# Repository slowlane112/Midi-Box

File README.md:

# MIDI Box

The MIDI Box is a stand-alone music box built around an ESP32-S3 and a SAM2695 General MIDI synth.
It plays MIDI files from an SD card, lets you record and edit your own songs, teaches you to play
the piano, and shows the music on a second screen with 14 visualisers. Plug in a MIDI keyboard
(two DIN inputs or Bluetooth) and play it through the box's own sound.

- **Player**: plays .mid files with tempo, transpose, play modes, mute and solo.
- **Studio**: records, edits and exports your own songs, with or without a keyboard.
- **Learn**: Play Along, scales and chords, Note Reading and Ear Training, with scores and stars.
- **Live In**: play your keyboard through the synth.
- **Visualisers**: 14 ways to watch the music on the bar screen.
- **Transfer**: send songs from your PC to the box.

*The back, left to right: USB-C (power and computer), audio out (red = right, white = left), the
micro SD card slot, then MIDI Thru, MIDI Out and MIDI In 1. MIDI In 2 is on the front.*

The home screen lists everything on screen 1. Screen 2 shows the firmware version, the song you can
resume, and the box's status: free space on the SD card, sound bank, keyboard sound, which DIN input
is in use and the display colour.

---

## The buttons

The buttons do the same thing on every screen.

| Button | Where it is | What it does |
|---|---|---|
| 1 | left of screen 1, the single button at the top | **Shift**: hold it and the bottom row of screen 1 shows the Shift functions |
| 2 / 3 | left of screen 1, the pair below it | Up / down (previous / next) |
| 4 – 8 | the row of five under screen 1, left to right | Soft keys, labelled along the bottom of screen 1. 4 is always **Back**, 8 the main action |
| 9 | under screen 2, left | Next visualiser on screen 2 (Shift + 9: previous) |
| 10 | under screen 2, middle | Next visualiser option: shape, speed, trails… (Shift + 10: previous) |
| 11 | under screen 2, right | Next visualiser colour (Shift + 11: previous) |
| 12 / 13 | right of the MIDI socket, top and bottom | Volume up / down, from any screen |

Holding **button 1** while switching on puts the ESP32-S3 into programming mode (see
*Installing the firmware*).

---

## Player

Pick **Player** on the home screen to browse the SD card. The browser shows folders and MIDI files
and opens in the folder you last played from. From it you can play, copy, move, rename and delete
files, and make new folders.

While a song plays, screen 1 shows the title, its place in the folder, the time, the tempo,
transpose and sound bank, and a level meter for each of the 16 channels.

- **Play modes** (Shift + 4): **Once**, **Repeat**, **Folder** (play the whole folder) and
  **Shuffle** (the folder in a random order).
- **Tempo** 25 – 200 %, **Transpose** ±12 semitones (drums stay as they are).
- **Sound bank**: General MIDI or Roland MT-32.
- **Tracks** (Shift + 8): turn any part off with **Sound**, hear one part on its own with **Solo**,
  or hide a part from the visualisers.
- **Resume** on the home screen carries on where you left off.
- **Auto play** (in Settings) decides whether a song starts as soon as you open it or waits for Play.
- Files that can't be played say why: *This is not a MIDI file we can play*, *Incomplete file*,
  *Could not read the file* or *Not enough memory for this file*. In Folder and Shuffle the box
  moves on to the next song after 3 seconds.

---

## Studio

Make your own songs in **projects** of up to 16 tracks.

- Choose a track and play your DIN or Bluetooth keyboard: you hear that track's instrument.
- **Record** with a count-in, metronome and optional loop for building up a part in layers. Keep or
  discard each take, and undo the last pass.
- **Edit** on a piano roll: copy, cut, paste, delete, duplicate, transpose, change velocity, and
  **quantise** (1/4 to 1/32 and triplets, with strength and swing).
- **Notes**: change single notes, or type a whole tune in with the buttons, no keyboard needed.
  Screen 2 shows the track as notation with note names.
- **Song settings**: tempo, beats per bar, length, GM or MT-32. **Track settings**: instrument (with
  a preview as you scroll), name, channel, volume, mute and solo.
- **Export .mid** (Shift + 5) saves a standard MIDI file you can play in the Player or on a PC.

---

## Learn

Learn to play with your MIDI keyboard connected. The first time, press the lowest and highest key of
your keyboard so the box knows its range.

- **Play Along**: 15 built-in pieces, from *Twinkle Twinkle* and *Ode to Joy* to *Für Elise*,
  *Clair de Lune* and the *Moonlight Sonata* (several in full and easy versions), or any MIDI file
  from the SD card. Play the right hand, left hand or both while the box plays the rest.
  - **Wait mode** waits for you to play each note. **Play mode** keeps going and grades every note
    *Perfect*, *Good*, *Miss* or *Wrong*, with a combo score.
  - Choose the speed, starting bar and count-in, loop four bars, or show note names.
  - Screen 2 is the game: notes fall onto a keyboard the size of yours.
  - Results give 1 – 3 stars, your score, best combo and whether you tend to play early or late.
- **Exercises**: major and minor scales, chords and arpeggios in every key, with the right fingering
  on a grand staff, played along to a metronome. A steadiness meter shows if you rush or drag.
- **Note Reading**: a note appears on the staff; play it before time runs out. Ledger lines, and
  later sharps and flats, come in as you get better.
- **Ear Training**: the box plays, you answer: same or different, up or down, intervals, major or
  minor chords. New levels unlock as you go.
- **Practice stats** on the home screen: your last sessions, total time, stars and songs learnt.

---

## Live In

Play a keyboard through the box's synth. Choose the input (back or front DIN socket, or Bluetooth),
the sound bank and the instrument, which you hear as you scroll through them. The screen shows
activity on each channel and the last message received.

- **Keyboard sound** (Shift + 8, or in Settings) turns the synth on or off for your keyboard. With
  it off the visualisers still follow what you play.
- **Panic** stops every sounding note.
- **Bluetooth MIDI**: 5 reconnects the last device, Shift + 5 searches for a new one.

The **MIDI Thru** socket passes everything from MIDI In 1 (the back socket) straight on to other
gear.

---

## Visualisers

Screen 2 shows the music while you play or listen. Button 9 steps through them, button 10 changes
the option and button 11 the colour. Hold Shift (button 1) with any of the three to go back one.
Each one remembers its own settings.

| Visualiser | Button 10 | Button 11 |
|---|---|---|
| **Piano**: keys light up, with note names and how hard each was played | note names on / off | key colour |
| **Spectrum Analyser**: 16 bars from 31 Hz to 16 kHz, the way a real analyser would show the sound | peak line on / off | bar colour |
| **Staff**: the music scrolling on a grand staff | all channels or one | by channel or one colour |
| **Chords**: the chord name, its notes and the progression | all channels or one | colour |
| **Piano Roll**: notes scrolling past | speed | background |
| **Constellation**: a glowing orb for every note in a starry sky | blobs on / off | background |
| **Embers**: sparks drift off every note, with turning rings behind | rings on / off | background |
| **Warp**: a twisting tunnel, with shapes that change on the drums | shape | background |
| **Psychedelic**: a swirling pattern with waves on the drums | shape | its own colours |
| **Pulse**: flowing plasma with rings for each note | ring shape | colour or Rainbow |
| **Fireworks**: a burst for every note under a starry sky | trails on / off | by channel or one colour |
| **Kaleidoscope**: mirrored shards for every note, rings for the drums | 6 / 8 / 12 slices | background |
| **Synthwave**: a retro sunset with mountains that move with the music | grid speed | theme: Classic, Outrun, Ice, Toxic |
| **Spirograph**: glowing curves shaped by the chords you play | trails on / off | colour or Rainbow |

The colours are Green, Blue, Amber, Purple, Pink, Cyan, Red and White. The last choice on button 11
is **Cycle**, which slowly fades from one colour to the next every 8 seconds.

---

## Getting songs onto the box

Copy .mid files onto the SD card with a card reader, in any folders you like, or send them from a
PC over Bluetooth:

- `extra/midi_box_transfer.py` sends one or more files from Linux or Windows.
  `--install` adds it to the right-click menu (Nemo on Linux, *Send to* on Windows).
  See `extra/midi_box_transfer.txt`.
- The box asks you to accept or decline, then saves the files in `/downloads`.

On the SD card:

| Folder | What's in it |
|---|---|
| any folder you like | your MIDI files (.mid) |
| `/downloads` | files sent from a PC |
| `/projects` | Studio projects (.mbp) and the .mid files you export |
| `/learn` | your keyboard range, best scores, stars and practice time |

---

## Settings

- **Display brightness** and **Display colour** (the highlight colour of the menus).
- **Sound bank**: General MIDI or Roland MT-32.
- **Keyboard sound**: play the MIDI inputs through the synth.
- **Auto play**: start a song as soon as it is opened, or wait for Play.
- **Visualiser**: which one is on screen 2.
- **About**: the firmware version.

---

## Building a MIDI Box

Everything plugs into one main board: the ESP32-S3 board sits on it, and every other part connects
to it with a 2-pin to 8-pin lead. You need to be comfortable soldering through-hole parts (and one
small surface-mount transistor).

### What you need

**Modules and panel parts**

| | Qty | Part | Used for |
|---|---|---|---|
|  | 1 | ESP32-S3 Development Board N16R8, 44 pin (DevKitC-1) | the brain |
|  | 1 | 2.4" 240 × 320 TFT LCD module (ST7789V, SPI, 8 pins) | screen 1 |
|  | 1 | 2.79" 142 × 428 bar-type IPS TFT LCD module (NV3007, SPI, 8 pins) | screen 2 |
|  | 1 | MIDI Digital Music Module SAM2695 | the synth |
|  | 1 | Micro SD card module (Open-Smart "TF Card Breakout") | songs and settings |
|  | 1 | USB Type-C female to DIP breakout board (HW-189) | power and USB |
|  | 4 | DIN 5-pin female round vertical socket | MIDI In 1, In 2, Out, Thru |
|  | 2 | Female RCA panel-mount socket (red and white) | audio out |
|  | 1 | 3.5 mm stereo audio plug | from the synth to the RCA sockets |
|  | 1 | 10 × 21 mm rocker switch KCD1 | power |
|  | 13 | Mini push button, 4.5 × 4.5 × 3.8 mm | the 13 buttons |

**Main board parts** (resistors ¼ W)

| Qty | Part | Where |
|---|---|---|
| 2 | 6N137 optocoupler (DIP-8) and a DIP-8 socket for each | IC1 MIDI In 2, IC2 MIDI In 1 |
| 1 | SN74HCT14N hex Schmitt trigger (DIP-14) and a DIP-14 socket | IC3 MIDI Out and Thru |
| 1 | AO3401A P-channel MOSFET (SOT-23, surface mount) | Q1 screen backlight |
| 4 | 10 kΩ resistor | R1, R2, R4, R6 |
| 6 | 220 Ω resistor | R3, R5, R7, R8, R9, R10 |
| 2 | 1N4148 diode | D1, D2 |
| 3 | 100 nF ceramic capacitor | C1, C2, C3 (one beside each chip) |
| 2 | 5.1 kΩ resistor | on the USB-C breakout (see below) |
| 2 | 1 × 22 female header, 2.54 mm | for the ESP32-S3 board |
| 2 | 1 × 8 female header | J7, J8 screens |
| 2 | 1 × 6 female header | J2 buttons 4–8, J9 SD card |
| 3 | 1 × 4 female header | J1 buttons 1–3, J3 buttons 9–11, J10 USB-C |
| 2 | 1 × 3 female header | J4 buttons 12–13, J6 synth |
| 5 | 1 × 2 female header | J5 power switch, J11 – J14 MIDI sockets |
| 1 | 90 × 70 mm prototype board, 2.54 mm pitch | the main board |
| – | small pieces of prototype board | four strips for the buttons, and one to mount the USB-C breakout |

**Screws**

| Qty | Screw | Used for |
|---|---|---|
| 25 | M2 × 6 mm | all the parts inside: screens, button strips, main board, USB-C board, SAM2695, SD module |
| 8 | M3 × 8 mm button head | front panel to the case |
| 6 | M3 × 25 mm socket cap head | case top to case bottom |

You also need the 3D-printed case and parts (see [The case](#the-case)), leads with 2.54 mm pins or
housings to join each part to its header (Dupont leads, crimped housings or wire soldered to header
pins all work), a micro SD card, and a USB-C power supply or cable.

### The main board

Build the board on a standard **90 × 70 mm prototype board**: the case's screw holes are made to
fit it (four M2 holes, 2 mm in from each corner, 86 × 66 mm apart). A PCB design of the same board
is included too, but it has not been made or tested yet: see
[*The PCB (work in progress)*](#the-pcb-work-in-progress) below.

**Circuit**

*MIDI In 1 and 2, MIDI Out and MIDI Thru:*

*The ESP32-S3 board, the GPIO0 pull-up and the screen backlight switch:*

*The connectors, pin 1 at the top of each:*

Labels with the same name are joined: every `GPIO17` is one wire, every `GND` is one wire, and so on.
The ESP32-S3 board supplies the 3.3 V; the 5 V comes from the USB-C socket through the power switch.

**The prototype board build (tested)**

*The ESP32-S3 board runs along the bottom, USB end on the left and its antenna on the right, clear
of everything else. The 74HCT14 (left) and the two 6N137s sit in sockets along the top, each with
its 100 nF capacitor beside it and its resistors and diode next to it. The connector headers are a
long row across the middle and two columns down the right-hand side. The AO3401A is on the
underside, so you can't see it here.*

Keep the area to the right of the ESP32-S3 board's antenna free of wires and copper, so Bluetooth
works well.

**PCB layout** (top view, the square pad is pin 1 of each part). This is how the parts sit on the
PCB design. It is laid out differently from the prototype board above, and you don't have to copy
either one exactly: any layout that makes the connections in the circuit works.

**Soldering order**

1. **Q1** (AO3401A) first, while the board is flat: pin 1 (gate) to R1 and GPIO10, pin 2 (source)
   to 3.3 V, pin 3 (drain) to the BL pin of both screen headers. On a prototype board it can go on
   the **underside**, as in the photo; its three pins still connect the same way.
2. **Resistors** and **diodes**. Each 1N4148 goes across the LED of its 6N137, with the **band
   (cathode) to pin 2** and the other end to pin 3.
3. **IC sockets**, with the notch at pin 1, then the **capacitors**, each from 5 V to GND right next
   to its chip.
4. **Headers**: the two 1 × 22 rows for the ESP32-S3 board (11 holes apart, 27.94 mm), then the
   connector headers.
5. Check every joint, then fit the chips into their sockets, notch to notch.

### The PCB (work in progress)

> ⚠️ **Not tested.** This PCB has not been manufactured or tried in a MIDI Box yet. It is shared so
> you can see where the project is going, check it, or improve it. If you order it, you do so at your
> own risk. The prototype-board build above is the one that is known to work.

The KiCad project is in [`hardware/main_board/`](hardware/main_board/):

| File | What it is |
|---|---|
| `midibox_main.kicad_sch` | the circuit (the same as the pictures above) |
| `midibox_main.kicad_pcb` | the 90 × 70 mm, 2-layer board, routed, with a ground pour on both sides |
| `midibox_main.kicad_pro` | the KiCad project with the track widths and clearances |
| `BOM.csv` | the parts on the board |
| `WIRING.md` | every connection, net by net |
| `midibox_main_gerbers.zip` | the Gerber and drill files, ready to upload to a PCB maker |
| `gerbers/` | the same Gerber and drill files, unzipped |

It uses the same parts, the same connectors and the same pin order as the prototype-board build, so
everything else in this guide applies to it. The four M2 holes are in the same places.

**Where it stands**

- It was drawn and routed in KiCad 10 and passes its design-rule check with these known exceptions:
  - Some resistor, diode and capacitor outlines overlap slightly on paper. The real parts sit about
    1 mm apart.
  - One GND pin of the ESP32-S3 board (the bottom row, at the right-hand end) is not joined to
    the board's ground, because it sits next to the antenna area, which is kept free of copper.
    The ESP32-S3 board joins all its GND pins itself.
  - The pin labels on the silkscreen are a little smaller than some makers like (0.7 mm).
- Nothing on the board has been checked on real hardware: the footprints against your actual
  parts, the ESP32-S3 board's two pin rows (27.94 mm apart), the MOSFET's pinout, or the board
  in the case.

**If you want to try it**

1. Open the project in KiCad and run **Inspect → Design Rules Checker** yourself.
2. Compare each footprint with the parts you have, especially the ESP32-S3 board and Q1 (AO3401A).
3. Upload `midibox_main_gerbers.zip` to a PCB maker: 2 layers, 90 × 70 mm, 1.6 mm thick. (If you
   change the design, make new ones with **File → Fabrication Outputs**.)
4. Please share what you find. Corrections will go into a tested version.

### Connecting the parts

Pin 1 of each header is the square pad in the layout above. All the button and screen headers have
pin 1 (and GND) at the bottom.

**Screens**: both modules have the same 8 pins in the same order, so each plugs in pin for pin.

| Header pin | 1 | 2 | 3 | 4 | 5 | 6 | 7 | 8 |
|---|---|---|---|---|---|---|---|---|
| Screen pin | GND | VCC / VDD | SCL | SDA | RES | DC | CS | BL |
| J7 screen 1 (2.4") | GND | 3.3 V | GPIO15 | GPIO6 | GPIO13 | GPIO21 | GPIO12 | backlight |
| J8 screen 2 (2.79") | GND | 3.3 V | GPIO8 | GPIO7 | GPIO14 | GPIO18 | GND | backlight |

**SD card module (J9)**: 6 of its 9 pins. Leave CDN, DAT1 and DAT2 unconnected.

| J9 pin | 1 | 2 | 3 | 4 | 5 | 6 |
|---|---|---|---|---|---|---|
| Module pin | GND | VCC | DO | DI | SCLK | CS |

**Synth (J6)**: to the SAM2695's 3-pin **MIDI** connector: pin 1 → **G**, pin 2 → **V**,
pin 3 → **S**.

**Audio**: solder a short cable from the 3.5 mm plug to the two RCA sockets and plug it into the
SAM2695's headphone jack:

- **Tip** → left RCA (white)
- **Ring** → right RCA (red)
- **Sleeve** → the ground tag of both RCA sockets

**USB-C (J10)**: the breakout is soldered by its header pins onto a small piece of prototype board,
which is screwed into the case behind the USB-C hole.

The HW-189 has 12 pins in two columns (rows counted from the GND end):

| Row | Inner column (next to the labels) | Outer column |
|---|---|---|
| 1 | GND | GND |
| 2 | SBU1 | **CC2** |
| 3 | DN1 | DP2 |
| 4 | DP1 | DN2 |
| 5 | **CC1** | SBU2 |
| 6 | VCC | VCC |

1. On the mounting board, solder **one 5.1 kΩ resistor from CC1 to GND** and **another from CC2 to
   GND**. Use two separate resistors. Without them a USB-C charger or a C-to-C cable won't switch the
   5 V on.
2. Join the two **GND** pins, and the two **VCC** pins.
3. Link **DN1 to DN2** and **DP1 to DP2** (the short blue and yellow links in the photo) so the plug
   works either way up. Leave SBU1 and SBU2 unconnected.
4. Connect it to J10:

| J10 pin | 1 | 2 | 3 | 4 |
|---|---|---|---|---|
| Breakout | VCC | GND | DP (D+) | DN (D−) |

**Power switch (J5)**: the rocker switch goes between pin 1 (the ESP32-S3 board's 5 V) and pin 2
(5 V from the USB-C socket).

**Back panel**: this is where each socket goes (seen from the back of the box). MIDI In 2 is the
one on the front panel.

**MIDI sockets**: two wires each. Header **pin 1 → DIN pin 4**, **pin 2 → DIN pin 5**. Pin 2 of the
DIN socket is the centre one, with 4 and 5 either side of it; check the numbers on your socket.

| Header | Socket |
|---|---|
| J14 | MIDI In 1 (back) |
| J11 | MIDI In 2 (front) |
| J13 | MIDI Out |
| J12 | MIDI Thru |

**Buttons**: numbered as in the picture under *The buttons*. Each button goes between its pin and
the GND pin of the same header. The 4-pin push
buttons are joined in pairs inside, so use two pins on opposite corners.

| Header | Pin 1 | Pin 2 | Pin 3 | Pin 4 | Pin 5 | Last pin |
|---|---|---|---|---|---|---|
| J1 | button 1 (Shift) | button 2 (up) | button 3 (down) | GND | | |
| J2 | button 4 (Back) | button 5 | button 6 | button 7 | button 8 | GND |
| J3 | button 9 | button 10 | button 11 | GND | | |
| J4 | button 12 | button 13 | GND | | | |

Label each lead as you make it, and keep each connector's leads together in a bundle held with a
couple of small clips. It keeps the inside tidy, and you can follow every lead when checking it.

### The case

The case and its small parts are 3D printed. The print files are in
[`hardware/case/`](hardware/case/); the screws are listed under [What you need](#what-you-need).

| File | Print | What it's for |
|---|---|---|
| `case_bottom.stl` | 1 | bottom half of the case |
| `case_top.stl` | 1 | top half of the case |
| `case_front.stl` | 1 | front panel |
| `button_main.stl` | 13 | button caps (see the note below) |
| `button_small_tolerance.stl` | – | looser button cap, only if needed |
| `button_high_tolerance.stl` | – | loosest button cap, only if needed |
| `midi_module_bottom_mount.stl` | 1 | goes under the SAM2695 module |
| `midi_module_top_washer.stl` | 2 | go on top of the SAM2695 module, under the screw heads |
| `screen_2_clamp.stl` | 1 | holds down the side of screen 2 that has no mounting holes |
| `sd_card_gap_fill.stl` | 1 | glued to the SD card module (see below) |
| `front_label_plate.stl` | 1 | front label |
| `back_label_plate.stl` | 1 | back label |

- **Button caps:** print one `button_main` first and try it. If it doesn't move freely when you
  press it, try `button_small_tolerance`, and if that is still tight, `button_high_tolerance`. Then
  print all 13 in the size that works.
- **SAM2695 module:** its mounting holes are extra large, so a screw head alone won't hold it. Fit
  the printed bottom mount under the module and a top washer over each hole.
- **SD card gap fill:** glue it to the SD card module. It closes the gap between the module and the
  case, so a card can't be pushed into the case instead of into the module's slot.
- **Tip:** for a perfect alignment of the screens in the front panel, you can enlarge the mounting
  holes on the LCD screen boards slightly. This gives each screen a little room to move so you can
  line it up exactly before tightening the screws.

**The front panel**

*Seen from behind, so left and right are swapped. The two screens are screwed to the panel; the
2.79" bar screen has a printed holder over its 8-pin header. The buttons are soldered onto four
small strips of prototype board, each held by two screws, with the buttons pushing through the
panel under the red caps: buttons 1–3 (on the right here), 4–8 (long strip at the bottom), 9–11
(middle strip) and 12–13 (small strip on the left). MIDI In 2 and the power switch are mounted
straight into the panel.*

**Fitting it into the case**

*First, before any wiring: the front panel is fitted, and the main board with the ESP32-S3 sits in
the base. The two posts on the left are for the SAM2695 module. On the back panel, from the left:
USB-C, the SD slot, the RCA sockets, and the three MIDI sockets. The RCA sockets can go either way
up, as long as the plug's tip goes to the white one and its ring to the red one.*

*Then everything wired up. The SD module, RCA sockets and USB-C breakout are fixed along the back
wall, the SAM2695 is screwed down on spacers on the right, and each connector's leads run to the
main board in their own clipped bundle.*

### Installing the firmware

1. Download the `.bin` file from the releases page.
2. Download **esptool** from https://github.com/espressif/esptool/releases.
3. Hold **button 1** while switching the box on to put it into programming mode, then connect the
   box's USB-C socket to your computer.
4. Flash the image:

   **Windows**
   ```
   esptool.exe --chip esp32s3 write_flash 0x0 "Midi_Box_x.x.x.bin"
   ```
   Replace `Midi_Box_x.x.x.bin` with the name of your file.

   **Linux**
   ```
   ./esptool --chip esp32s3 write_flash 0x0 Midi_Box_*.bin
   ```
   If esptool can't find the box, add the `--port` option, for example `--port COM5` on Windows or
   `--port /dev/ttyACM0` on Linux.
5. Switch the box off and on again.

**Building it yourself:** install ESP-IDF 6.0, then run `idf.py set-target esp32s3` and
`idf.py build flash`.

You can also flash the ESP32-S3 board through its own USB-C ports before it goes into the box. In
the finished box those ports aren't used.

### First switch-on

- Both screens light up after a moment: the home menu on screen 1 and the status on screen 2.
- **A screen stays dark or white**: check its 8 wires, the 3.3 V, and the backlight (BL) wire.
- **A button does nothing**: check the GND wire of its header.
- **No sound**: check the synth's G / V / S wiring and the audio cable, and press button 12 to turn
  the volume up.
- **MIDI keyboard not heard**: open **Live In**; if the activity lights don't move, swap the two
  wires of that MIDI socket.
- **SD card: no card** on screen 2: check the 6 SD wires and that the card is FAT32.

**Tip: power it from a USB adapter.** A computer's USB port often can't supply enough current for the
MIDI Box. If it can't, the box will now and then reset itself (a "brownout"). For normal use, run it
from a USB wall adapter. If your computer can't power it reliably, only use the computer while you're
putting the firmware on.

### The SD card

Use a micro SD card formatted as **FAT32**. Copy your MIDI files into any folders you like; the box
makes its own folders (`/downloads`, `/projects`, `/learn`) when it needs them.

---

*Credits: the Moonlight Sonata arrangements in Learn come from the Mutopia Project (CC BY-SA 2.5),
see `tools/learn_midi/CREDITS.txt`.*

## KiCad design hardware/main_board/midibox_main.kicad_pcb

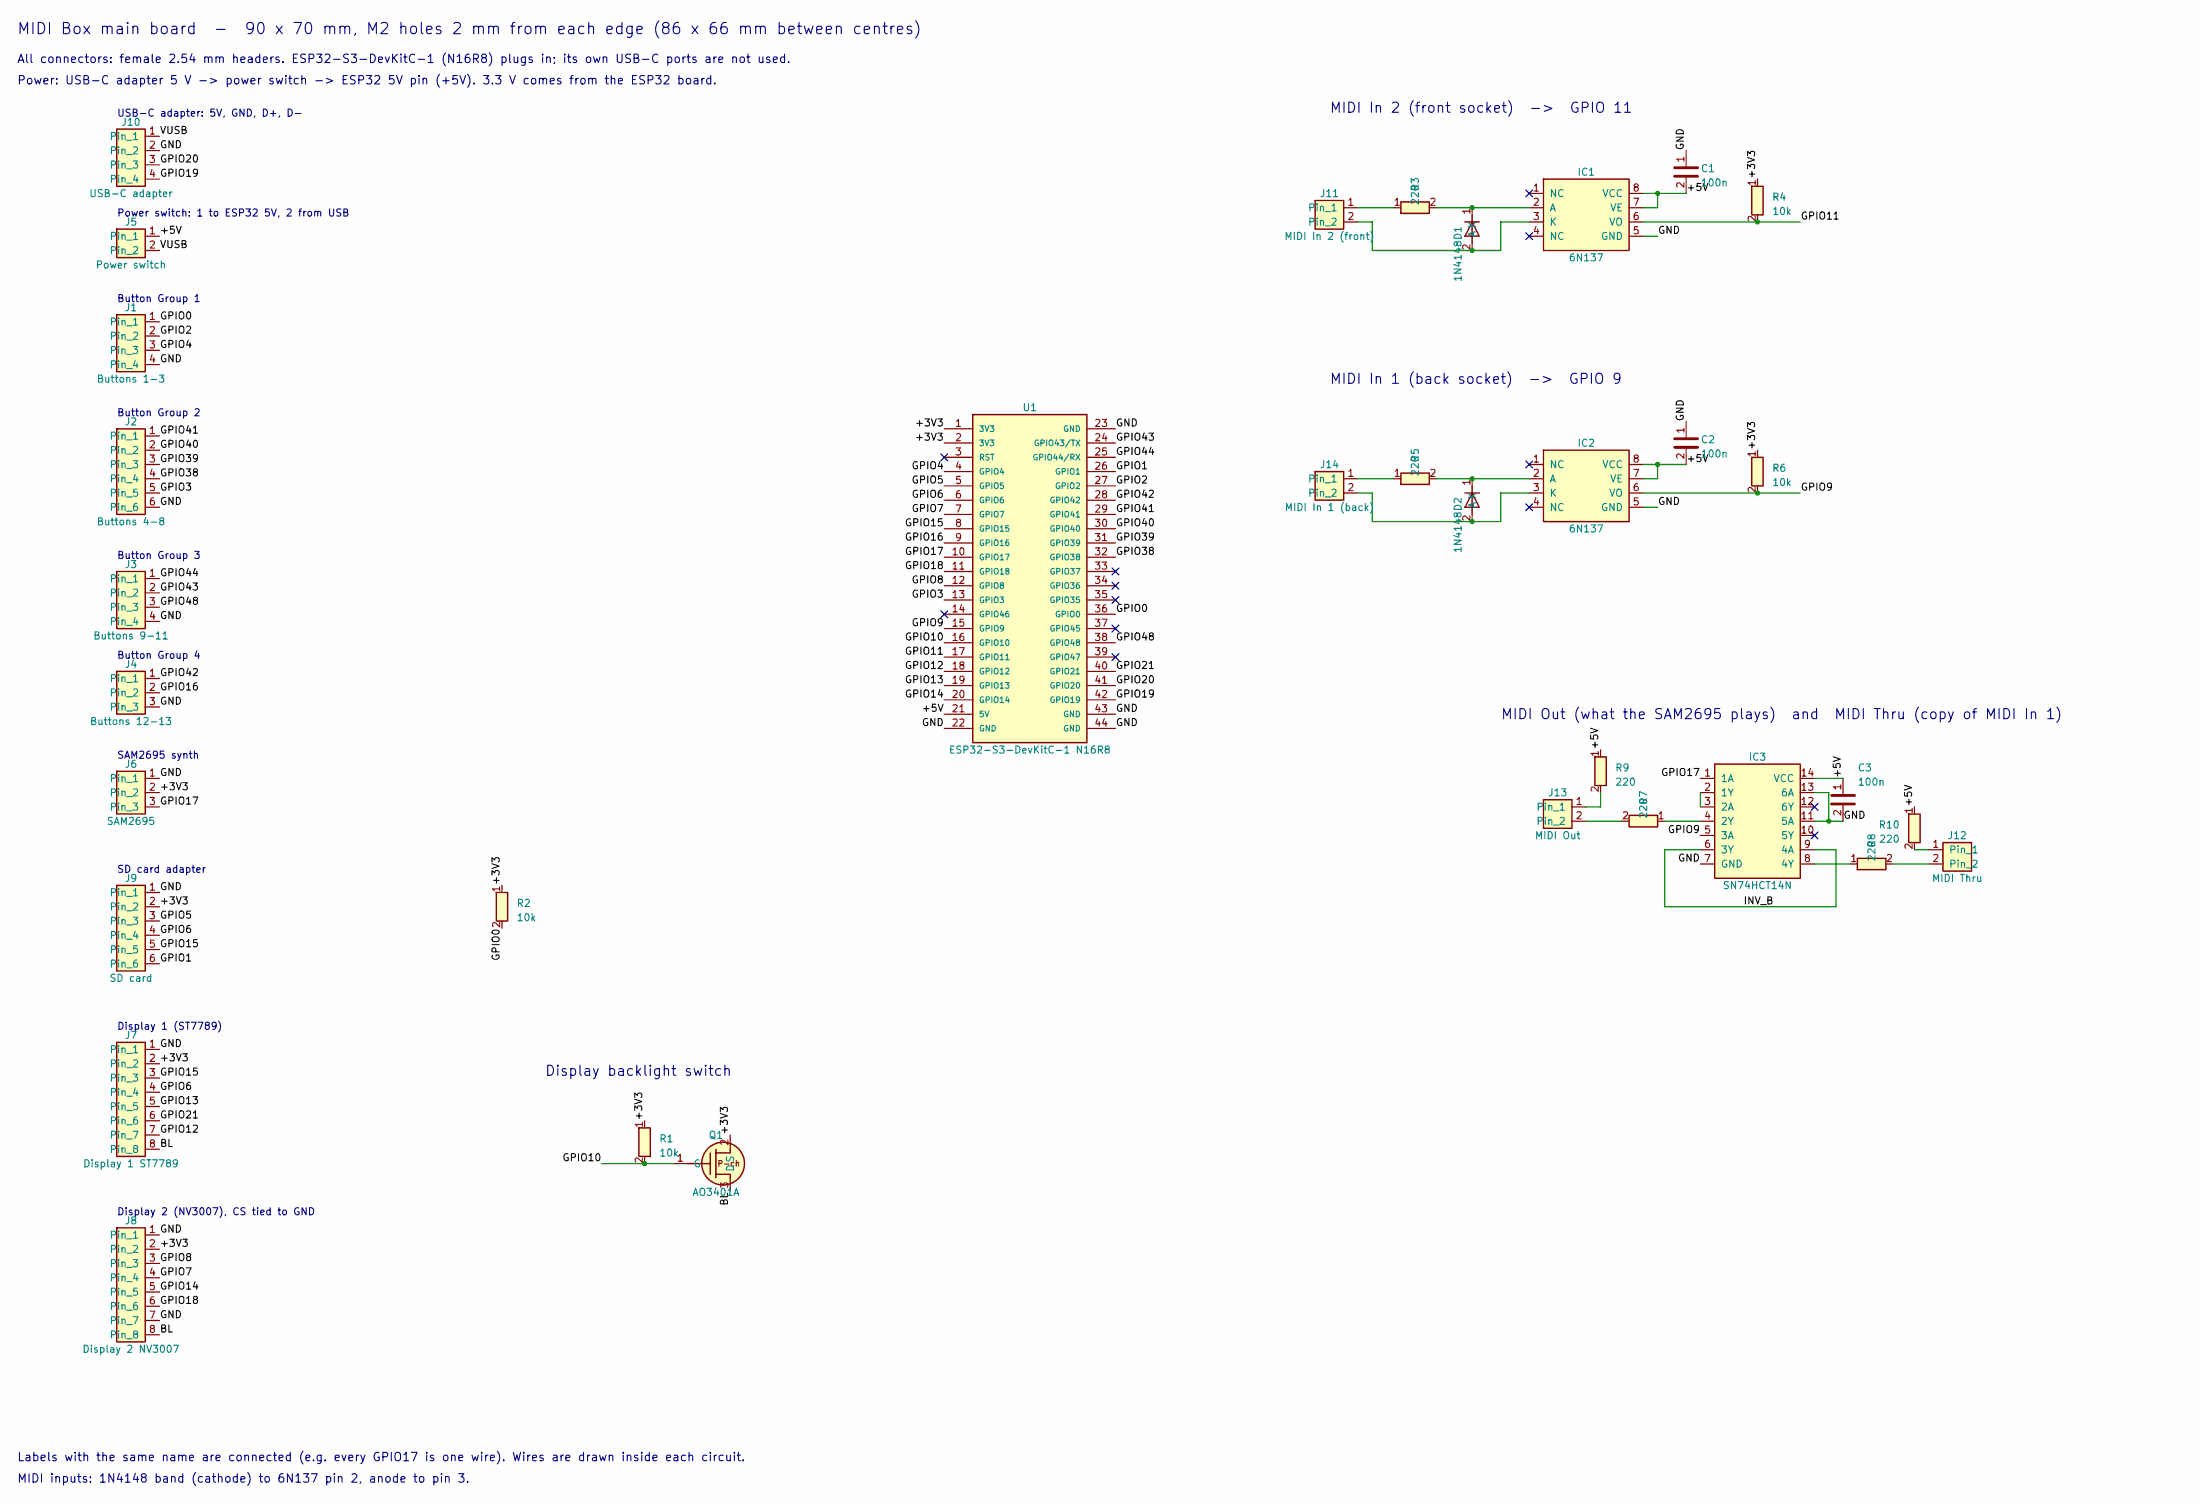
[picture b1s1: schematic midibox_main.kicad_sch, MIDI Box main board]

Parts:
C1, C2, C3: 100n; C_Disc_D3.0mm_W2.0mm_P2.54mm
D1, D2: 1N4148; D_DO-35_SOD27_P7.62mm_Horizontal
IC1, IC2: 6N137; DIP-8_W7.62mm_Socket
IC3: SN74HCT14N; DIP-14_W7.62mm_Socket
J1: Buttons 1-3; PinSocket_1x04_P2.54mm_Vertical
J2: Buttons 4-8; PinSocket_1x06_P2.54mm_Vertical
J3: Buttons 9-11; PinSocket_1x04_P2.54mm_Vertical
J4: Buttons 12-13; PinSocket_1x03_P2.54mm_Vertical
J5: Power switch; PinSocket_1x02_P2.54mm_Vertical
J6: SAM2695; PinSocket_1x03_P2.54mm_Vertical
J7: Display 1 ST7789; PinSocket_1x08_P2.54mm_Vertical
J8: Display 2 NV3007; PinSocket_1x08_P2.54mm_Vertical
J9: SD card; PinSocket_1x06_P2.54mm_Vertical
J10: USB-C adapter; PinSocket_1x04_P2.54mm_Vertical
J11: MIDI In 2 (front); PinSocket_1x02_P2.54mm_Vertical
J12: MIDI Thru; PinSocket_1x02_P2.54mm_Vertical
J13: MIDI Out; PinSocket_1x02_P2.54mm_Vertical
J14: MIDI In 1 (back); PinSocket_1x02_P2.54mm_Vertical
Q1: AO3401A; SOT-23
R1, R2, R4, R6: 10k; R_Axial_DIN0207_L6.3mm_D2.5mm_P10.16mm_Horizontal
R3, R5, R7, R8, R9, R10: 220; R_Axial_DIN0207_L6.3mm_D2.5mm_P10.16mm_Horizontal
U1: ESP32-S3-DevKitC-1 N16R8; ESP32-S3-DevKitC-1_2x22_W27.94mm

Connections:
+3V3: J6.2 (+3V3), J7.2 (+3V3), J8.2 (+3V3), J9.2 (+3V3), Q1.2 (S), R1.1 (+3V3), R2.1 (+3V3), R4.1 (+3V3), R6.1 (+3V3), U1.1 (3V3), U1.2 (3V3)
+5V: C1.2 (+5V), C2.2 (+5V), C3.1 (+5V), IC1.7 (VE), IC1.8 (VCC), IC2.7 (VE), IC2.8 (VCC), IC3.14 (VCC), J5.1 (+5V), R9.1 (+5V), R10.1 (+5V), U1.21 (5V)
BL: J7.8 (BL), J8.8 (BL), Q1.3 (D)
GND: C1.1 (GND), C2.1 (GND), C3.2 (GND), IC1.5 (GND), IC2.5 (GND), IC3.7 (GND), IC3.11 (5A), IC3.13 (6A), J1.4 (GND), J2.6 (GND), J3.4 (GND), J4.3 (GND), J6.1 (GND), J7.1 (GND), J8.1 (GND), J8.7 (GND), J9.1 (GND), J10.2 (GND), U1.22 (GND), U1.23 (GND), U1.43 (GND), U1.44 (GND)
GPIO0: J1.1 (GPIO0), R2.2 (GPIO0), U1.36 (0)
GPIO1: J9.6 (GPIO1), U1.26 (1)
GPIO2: J1.2 (GPIO2), U1.27 (2)
GPIO3: J2.5 (GPIO3), U1.13 (3)
GPIO4: J1.3 (GPIO4), U1.4
GPIO5: J9.3 (GPIO5), U1.5
GPIO6: J7.4 (GPIO6), J9.4 (GPIO6), U1.6
GPIO7: J8.4 (GPIO7), U1.7
GPIO8: J8.3 (GPIO8), U1.12 (8)
GPIO9: IC2.6 (VO), IC3.5 (3A), R6.2 (GPIO9), U1.15 (9)
GPIO10: Q1.1 (G), R1.2 (GPIO10), U1.16 (10)
GPIO11: IC1.6 (VO), R4.2 (GPIO11), U1.17 (11)
GPIO12: J7.7 (GPIO12), U1.18 (12)
GPIO13: J7.5 (GPIO13), U1.19 (13)
GPIO14: J8.5 (GPIO14), U1.20 (14)
GPIO15: J7.3 (GPIO15), J9.5 (GPIO15), U1.8 (15)
GPIO16: J4.2 (GPIO16), U1.9 (16)
GPIO17: IC3.1 (1A), J6.3 (GPIO17), U1.10 (17)
GPIO18: J8.6 (GPIO18), U1.11 (18)
GPIO19: J10.4 (GPIO19), U1.42 (19)
GPIO20: J10.3 (GPIO20), U1.41 (20)
GPIO21: J7.6 (GPIO21), U1.40 (21)
GPIO38: J2.4 (GPIO38), U1.32 (38)
GPIO39: J2.3 (GPIO39), U1.31 (39)
GPIO40: J2.2 (GPIO40), U1.30 (40)
GPIO41: J2.1 (GPIO41), U1.29 (41)
GPIO42: J4.1 (GPIO42), U1.28 (42)
GPIO43: J3.2 (GPIO43), U1.24 (TX)
GPIO44: J3.1 (GPIO44), U1.25 (RX)
GPIO48: J3.3 (GPIO48), U1.38 (48)
HC_OUT: IC3.4 (2Y), R7.1 (HC_OUT)
HC_THRU: IC3.8 (4Y), R8.1 (HC_THRU)
INV_A: IC3.2 (1Y), IC3.3 (2A)
INV_B: IC3.6 (3Y), IC3.9 (4A)
MIDI1_A: D2.1 (K), IC2.2 (A), R5.2 (MIDI1_A)
MIDI1_K: D2.2 (A), IC2.3 (K), J14.2 (MIDI1_K)
MIDI1_SRC: J14.1 (MIDI1_SRC), R5.1 (MIDI1_SRC)
MIDI2_A: D1.1 (K), IC1.2 (A), R3.2 (MIDI2_A)
MIDI2_K: D1.2 (A), IC1.3 (K), J11.2 (MIDI2_K)
MIDI2_SRC: J11.1 (MIDI2_SRC), R3.1 (MIDI2_SRC)
MOUT_SRC: J13.1 (MOUT_SRC), R9.2 (MOUT_SRC)
MOUT_TX: J13.2 (MOUT_TX), R7.2 (MOUT_TX)
THRU_SRC: J12.1 (THRU_SRC), R10.2 (THRU_SRC)
THRU_TX: J12.2 (THRU_TX), R8.2 (THRU_TX)
VUSB: J5.2 (VUSB), J10.1 (VUSB)

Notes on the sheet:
Button Group 1
Button Group 2
Button Group 3
Button Group 4
USB-C adapter: 5V, GND, D+, D-
Display 1 (ST7789)
Display 2 (NV3007), CS tied to GND
Power switch: 1 to ESP32 5V, 2 from USB
SD card adapter
SAM2695 synth
MIDI In 2 (front socket) -> GPIO 11
MIDI In 1 (back socket) -> GPIO 9
MIDI Out (what the SAM2695 plays) and MIDI Thru (copy of MIDI In 1)
Display backlight switch
MIDI Box main board - 90 x 70 mm, M2 holes 2 mm from each edge (86 x 66 mm between centres)
All connectors: female 2.54 mm headers. ESP32-S3-DevKitC-1 (N16R8) plugs in; its own USB-C ports are not used.
Power: USB-C adapter 5 V -> power switch -> ESP32 5V pin (+5V). 3.3 V comes from the ESP32 board.
Labels with the same name are connected (e.g. every GPIO17 is one wire). Wires are drawn inside each circuit.
MIDI inputs: 1N4148 band (cathode) to 6N137 pin 2, anode to pin 3.

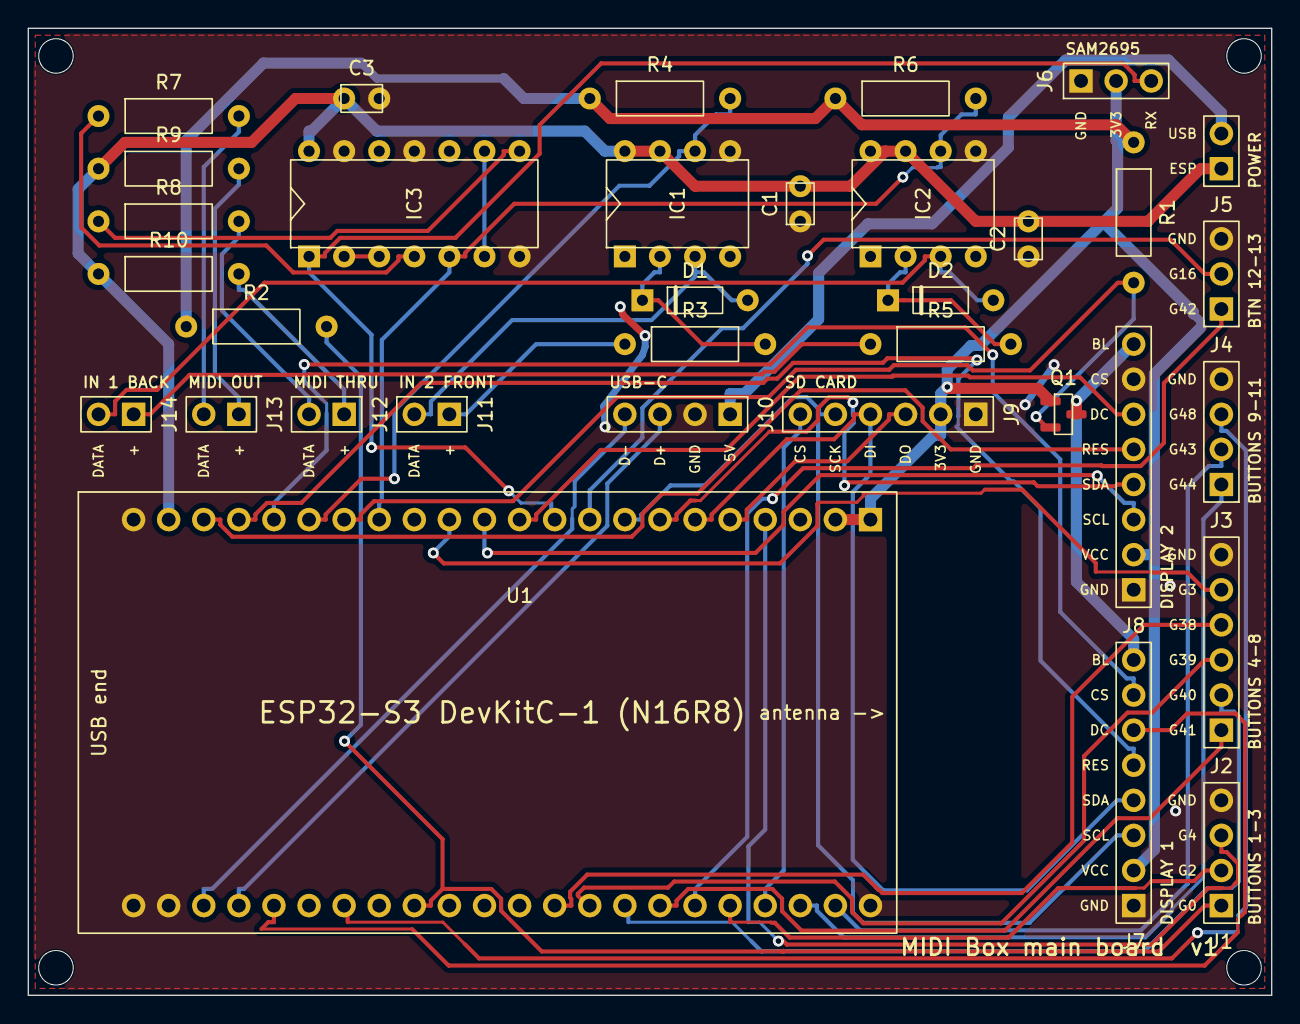
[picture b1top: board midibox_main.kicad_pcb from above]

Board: 2 copper layers, 90.0 x 70.0 mm, 38 parts (0 on the bottom side), 49 nets.

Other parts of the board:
H1, H2, H3, H4: M2; MountingHole_2.5mm

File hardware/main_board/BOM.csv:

Qty,Refs,Value,Part,Footprint
3,"C1 C2 C3",100n,Ceramic capacitor,Capacitor_THT:C_Disc_D3.0mm_W2.0mm_P2.54mm
2,"D1 D2",1N4148,Diode,Diode_THT:D_DO-35_SOD27_P7.62mm_Horizontal
4,"H1 H2 H3 H4",M2,M2 mounting hole (no part),MountingHole:MountingHole_2.5mm
2,"IC1 IC2",6N137,Optocoupler (DIP-8, use a socket),Package_DIP:DIP-8_W7.62mm_Socket
1,"IC3",SN74HCT14N,Hex Schmitt inverter (DIP-14, use a socket),Package_DIP:DIP-14_W7.62mm_Socket
3,"J1 J3 J10",1x4 female header,Female 2.54 mm header, straight,Connector_PinSocket_2.54mm:PinSocket_1x04_P2.54mm_Vertical
2,"J2 J9",1x6 female header,Female 2.54 mm header, straight,Connector_PinSocket_2.54mm:PinSocket_1x06_P2.54mm_Vertical
2,"J4 J6",1x3 female header,Female 2.54 mm header, straight,Connector_PinSocket_2.54mm:PinSocket_1x03_P2.54mm_Vertical
5,"J5 J11 J12 J13 J14",1x2 female header,Female 2.54 mm header, straight,Connector_PinSocket_2.54mm:PinSocket_1x02_P2.54mm_Vertical
2,"J7 J8",1x8 female header,Female 2.54 mm header, straight,Connector_PinSocket_2.54mm:PinSocket_1x08_P2.54mm_Vertical
1,"Q1",AO3401A,P-channel MOSFET SOT-23,Package_TO_SOT_SMD:SOT-23
4,"R1 R2 R4 R6",10k,Resistor 1/4 W,Resistor_THT:R_Axial_DIN0207_L6.3mm_D2.5mm_P10.16mm_Horizontal
6,"R3 R5 R7 R8 R9 R10",220,Resistor 1/4 W,Resistor_THT:R_Axial_DIN0207_L6.3mm_D2.5mm_P10.16mm_Horizontal
1,"U1",ESP32-S3-DevKitC-1 N16R8,ESP32-S3 dev board,MidiBox:ESP32-S3-DevKitC-1_2x22_W27.94mm
2,,DIP-8 IC socket,Optional,
1,,DIP-14 IC socket,Optional,
